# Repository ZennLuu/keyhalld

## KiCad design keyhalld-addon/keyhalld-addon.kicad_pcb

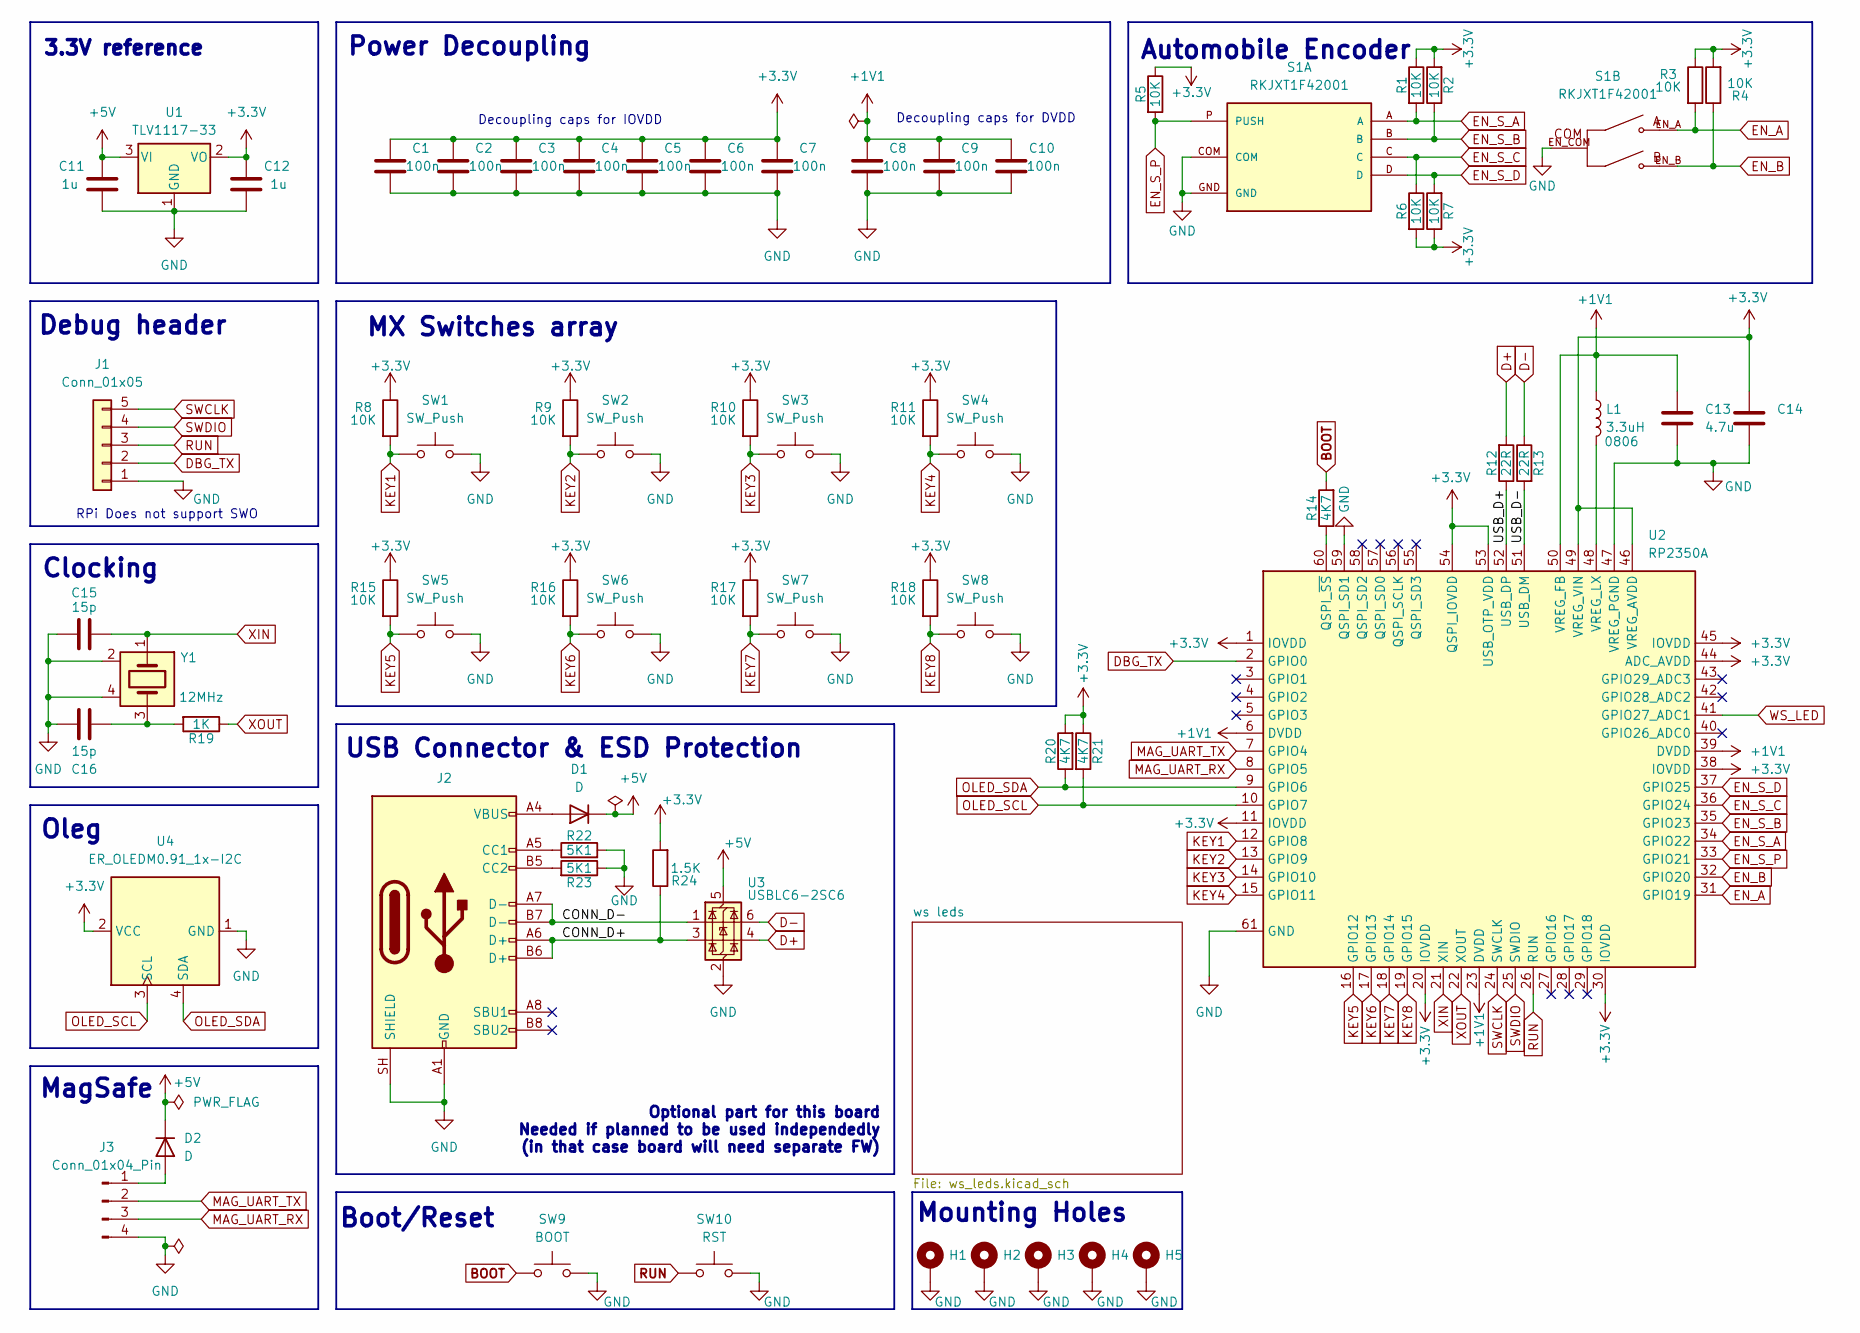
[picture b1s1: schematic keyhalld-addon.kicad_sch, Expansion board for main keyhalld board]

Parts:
C1, C2, C3, C4, C5, C6, C7, C8, C9, C10: 100n; C_0603_1608Metric_Pad1.08x0.95mm_HandSolder
C11, C12: 1u; C_0603_1608Metric_Pad1.08x0.95mm_HandSolder
C13, C14: 4.7u; C_0603_1608Metric
C15, C16: 15p; C_0603_1608Metric_Pad1.08x0.95mm_HandSolder
D1, D2: D; D_SOD-323
H1, H2, H3, H4, H5: MountingHole_Pad; MountingHole_2.2mm_M2_DIN965_Pad
J1: Conn_01x05; PinHeader_1x05_P2.54mm_Horizontal
J2: USB_C_Receptacle_USB2.0_16P; USB_C_Receptacle_GCT_USB4105-xx-A_16P_TopMnt_Horizontal
J3: Conn_01x04_Pin; PinHeader_1x04_P2.54mm_Vertical
L1: 3.3uH; L_Murata_DFE201610P
R1, R2, R3, R4, R5, R6, R7, R8, R9, R10, R11, R15, R16, R17, R18: 10K; R_0603_1608Metric_Pad0.98x0.95mm_HandSolder
R12, R13: 22R; R_0603_1608Metric_Pad0.98x0.95mm_HandSolder
R14, R20, R21: 4K7; R_0603_1608Metric_Pad0.98x0.95mm_HandSolder
R19: 1K; R_0603_1608Metric_Pad0.98x0.95mm_HandSolder
R22, R23: 5K1; R_0603_1608Metric_Pad0.98x0.95mm_HandSolder
R24: 1.5K; R_0603_1608Metric_Pad0.98x0.95mm_HandSolder
S1: RKJXT1F42001; XDCR_RKJXT1F42001
SW1, SW2, SW3, SW4, SW5, SW6, SW7, SW8: SW_Push; SW_Hotswap_Kailh_MX_1.00u
SW9: BOOT; SW_Tactile_SPST_NO_Straight_CK_PTS636Sx25SMTRLFS
SW10: RST; SW_Tactile_SPST_NO_Straight_CK_PTS636Sx25SMTRLFS
U1: TLV1117-33; SOT-223-3_TabPin2
U2: RP2350A; rpi_rp2350a_vias; part_uid RP-01HA9H-9K5E8T
U3: USBLC6-2SC6; SOT-23-6
U4: ER_OLEDM0.91_1x-I2C
Y1: 12MHz; Oscillator_SMD_Abracon_ASE-4Pin_3.2x2.5mm; tolerance 30ppm; part_uid RP-01G8X7-GS352B

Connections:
+1V1: C8.1, C9.1, C10.1, C13.1, L1.1, U2.6 (DVDD), U2.23 (DVDD), U2.39 (DVDD), U2.50 (VREG_FB)
+3.3V: C1.1, C2.1, C3.1, C4.1, C5.1, C6.1, C7.1, C12.1, C14.1, R1.1, R2.2, R3.1, R4.2, R5.1, R6.2, R7.1, R8.1, R9.1, R10.1, R11.1, R15.1, R16.1, R17.1, R18.1, R20.2, R21.1, R24.2, U1.2 (VO), U2.1 (IOVDD), U2.11 (IOVDD), U2.20 (IOVDD), U2.30 (IOVDD), U2.38 (IOVDD), U2.44 (ADC_AVDD), U2.45 (IOVDD), U2.46 (VREG_AVDD), U2.49 (VREG_VIN), U2.53 (USB_OTP_VDD), U2.54 (QSPI_IOVDD), U4.2 (VCC)
+5V: C11.1, D1.1 (K), D2.1 (K), U1.3 (VI), U3.5 (VBUS); also elsewhere on the board
/CONN_D+: J2.A6 (D+), J2.B6 (D+), R24.1, U3.3 (I/O2)
/CONN_D-: J2.A7 (D-), J2.B7 (D-), U3.1 (I/O1)
/USB_D+: R12.1, U2.52 (USB_DP)
/USB_D-: R13.2, U2.51 (USB_DM)
BOOT: R14.2, SW9.1
D+: R12.2, U3.4 (I/O2)
D-: R13.1, U3.6 (I/O1)
DBG_TX: J1.2, U2.2 (GPIO0)
EN_A: R3.2, S1.EN_A, U2.31 (GPIO19)
EN_B: R4.1, S1.EN_B, U2.32 (GPIO20)
EN_S_A: R1.2, S1.A, U2.34 (GPIO22)
EN_S_B: R2.1, S1.B, U2.35 (GPIO23)
EN_S_C: R6.1, S1.C, U2.36 (GPIO24)
EN_S_D: R7.2, S1.D, U2.37 (GPIO25)
EN_S_P: R5.2, S1.P (PUSH), U2.33 (GPIO21)
GND: C1.2, C2.2, C3.2, C4.2, C5.2, C6.2, C7.2, C8.2, C9.2, C10.2, C11.2, C12.2, C13.2, C14.2, C15.1, C16.1, H1.1 (1_1), H2.1 (1_1), H3.1 (1_1), H4.1 (1_1), H5.1 (1_1), J1.1, J2.A1 (GND), J2.A12 (GND), J2.B1 (GND), J2.B12 (GND), J2.SH (SHIELD), J3.4, R22.2, R23.1, S1.COM, S1.EN_COM, S1.GND, SW1.2, SW2.2, SW3.2, SW4.2, SW5.2, SW6.2, SW7.2, SW8.2, SW9.2, SW10.2, U1.1 (GND), U2.47 (VREG_PGND), U2.59 (QSPI_SD1), U2.61 (GND), U3.2 (GND), U4.1 (GND), Y1.2, Y1.4; also elsewhere on the board
KEY1: R8.2, SW1.1, U2.12 (GPIO8)
KEY2: R9.2, SW2.1, U2.13 (GPIO9)
KEY3: R10.2, SW3.1, U2.14 (GPIO10)
KEY4: R11.2, SW4.1, U2.15 (GPIO11)
KEY5: R15.2, SW5.1, U2.16 (GPIO12)
KEY6: R16.2, SW6.1, U2.17 (GPIO13)
KEY7: R17.2, SW7.1, U2.18 (GPIO14)
KEY8: R18.2, SW8.1, U2.19 (GPIO15)
MAG_UART_RX: J3.3, U2.8 (GPIO5)
MAG_UART_TX: J3.2, U2.7 (GPIO4)
unnamed: C16.2, R19.2, Y1.3
unnamed: D1.2 (A), J2.A4 (VBUS), J2.A9 (VBUS), J2.B4 (VBUS), J2.B9 (VBUS)
unnamed: D2.2 (A), J3.1
unnamed: J2.A5 (CC1), R22.1
unnamed: J2.B5 (CC2), R23.2
unnamed: R14.1, U2.60 (QSPI_~SS)
unnamed: L1.2, U2.48 (VREG_LX)
OLED_SCL: R21.2, U2.10 (GPIO7), U4.3 (SCL)
OLED_SDA: R20.1, U2.9 (GPIO6), U4.4 (SDA)
RUN: J1.3, SW10.1, U2.26 (RUN)
SWCLK: J1.5, U2.24 (SWCLK)
SWDIO: J1.4, U2.25 (SWDIO)
WS_LED: U2.41 (GPIO27_ADC1); also elsewhere on the board
XIN: C15.2, U2.21 (XIN), Y1.1
XOUT: R19.1, U2.22 (XOUT)

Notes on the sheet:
Automobile Encoder
Decoupling caps for IOVDD
Boot/Reset
Decoupling caps for DVDD
USB Connector & ESD Protection
Clocking
Oleg
RPi Does not support SWO
MX Switches array
Power Decoupling
Debug header
Mounting Holes
3.3V reference
MagSafe
Optional part for this board Needed if planned to be used independedly (in that case board will need separate FW)

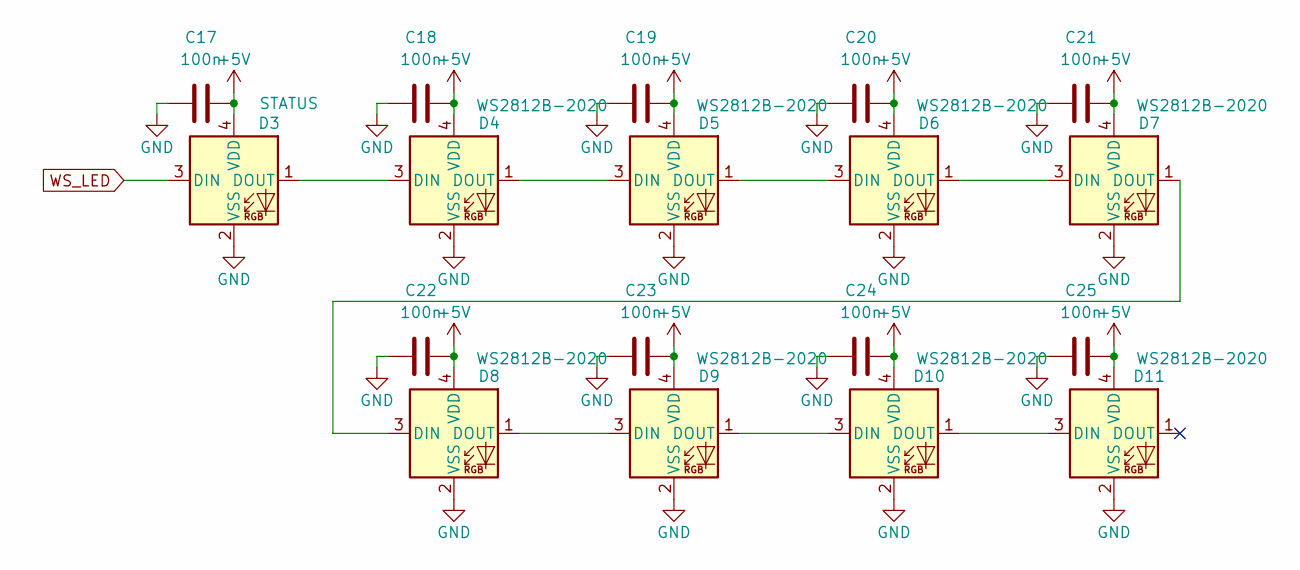
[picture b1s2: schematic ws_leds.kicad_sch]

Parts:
C17, C18, C19, C20, C21, C22, C23, C24, C25: 100n; C_0603_1608Metric
D3: STATUS; LED_WS2812B-2020_PLCC4_2.0x2.0mm
D4, D5, D6, D7, D8, D9, D10, D11: WS2812B-2020; LED_WS2812B-2020_PLCC4_2.0x2.0mm

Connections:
+5V: C17.2, C18.2, C19.2, C20.2, C21.2, C22.2, C23.2, C24.2, C25.2, D3.4 (VDD), D4.4 (VDD), D5.4 (VDD), D6.4 (VDD), D7.4 (VDD), D8.4 (VDD), D9.4 (VDD), D10.4 (VDD), D11.4 (VDD); also elsewhere on the board
GND: C17.1, C18.1, C19.1, C20.1, C21.1, C22.1, C23.1, C24.1, C25.1, D3.2 (VSS), D4.2 (VSS), D5.2 (VSS), D6.2 (VSS), D7.2 (VSS), D8.2 (VSS), D9.2 (VSS), D10.2 (VSS), D11.2 (VSS); also elsewhere on the board
unnamed: D3.1 (DOUT), D4.3 (DIN)
unnamed: D4.1 (DOUT), D5.3 (DIN)
unnamed: D5.1 (DOUT), D6.3 (DIN)
unnamed: D6.1 (DOUT), D7.3 (DIN)
unnamed: D7.1 (DOUT), D8.3 (DIN)
unnamed: D8.1 (DOUT), D9.3 (DIN)
unnamed: D9.1 (DOUT), D10.3 (DIN)
unnamed: D10.1 (DOUT), D11.3 (DIN)
WS_LED: D3.3 (DIN); also elsewhere on the board

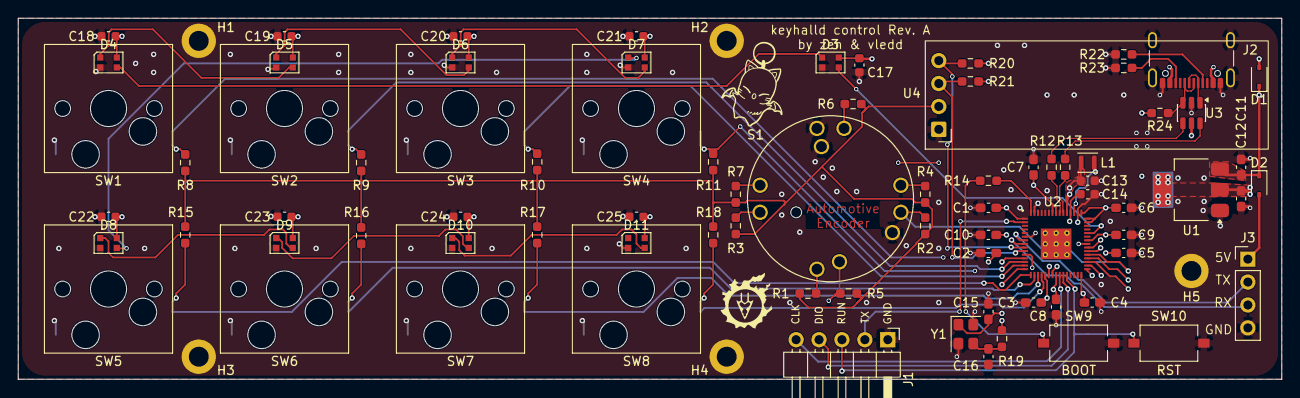
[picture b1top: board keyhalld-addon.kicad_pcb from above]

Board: 4 copper layers, 140.0 x 40.0 mm, 85 parts (0 on the bottom side), 52 nets.

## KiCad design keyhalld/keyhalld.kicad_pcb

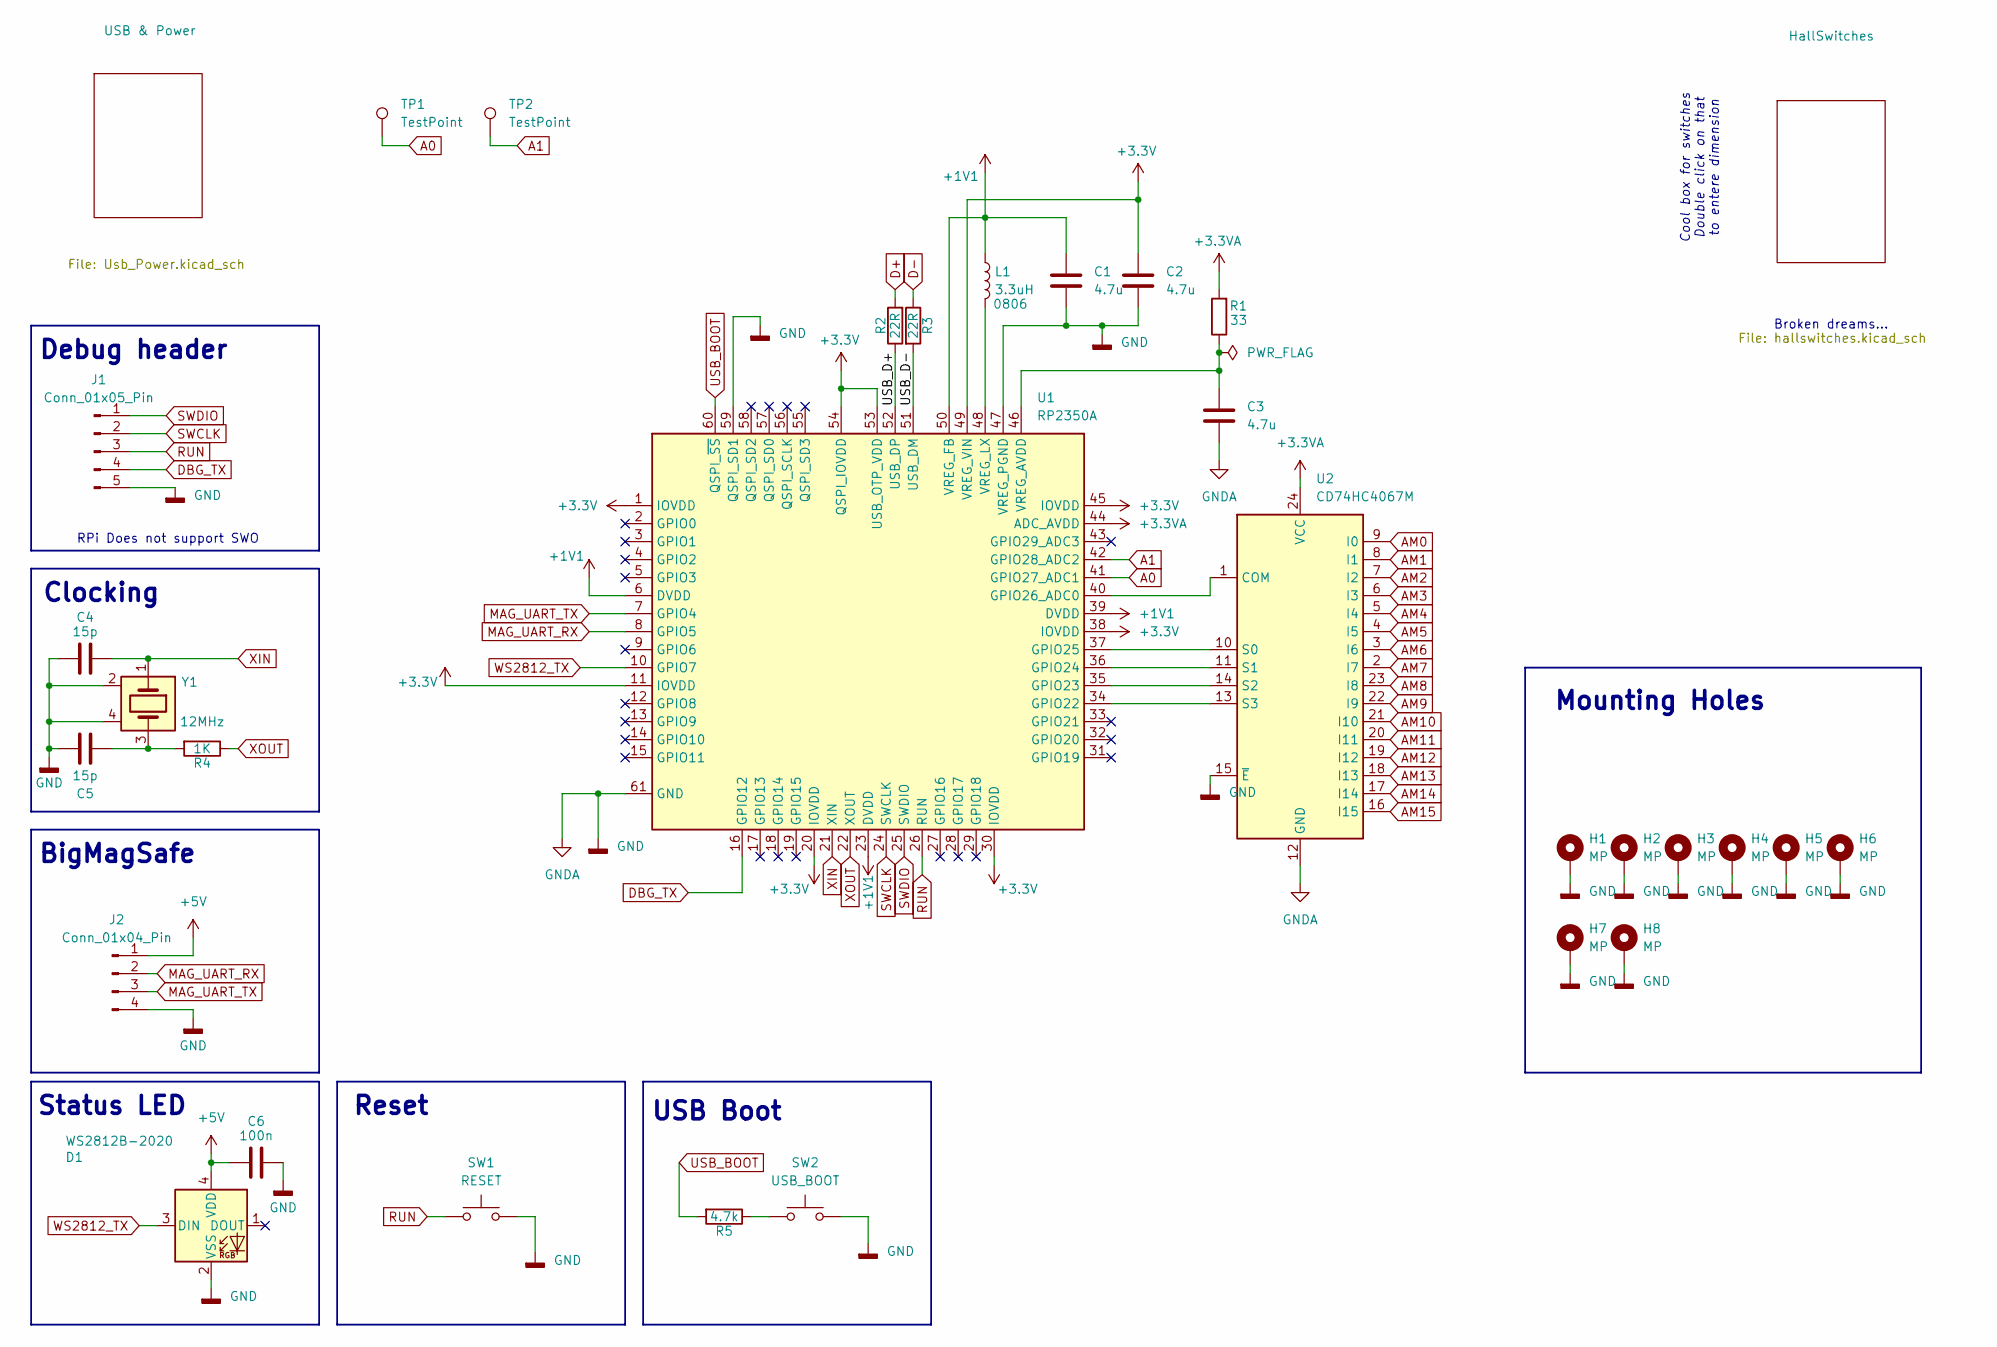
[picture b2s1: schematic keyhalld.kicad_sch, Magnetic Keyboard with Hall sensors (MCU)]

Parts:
C1, C2, C3: 4.7u; C_0603_1608Metric
C4, C5: 15p; C_0603_1608Metric_Pad1.08x0.95mm_HandSolder
C6: 100n; C_0603_1608Metric_Pad1.08x0.95mm_HandSolder
D1: WS2812B-2020; LED_WS2812B-2020_PLCC4_2.0x2.0mm
H1, H2, H3, H4, H5, H6, H7, H8: MP; MountingHole_3.2mm_M3_Pad
J1: Conn_01x05_Pin; PinHeader_1x05_P2.54mm_Horizontal
J2: Conn_01x04_Pin; PinHeader_1x04_P2.54mm_Vertical
L1: 3.3uH; L_Murata_DFE201610P
R1: 33; R_0603_1608Metric_Pad0.98x0.95mm_HandSolder
R2, R3: 22R; R_0603_1608Metric_Pad0.98x0.95mm_HandSolder
R4: 1K; R_0603_1608Metric_Pad0.98x0.95mm_HandSolder
R5: 4.7k; R_0603_1608Metric_Pad0.98x0.95mm_HandSolder
SW1: RESET; SW_Tactile_SPST_NO_Straight_CK_PTS636Sx25SMTRLFS
SW2: USB_BOOT; SW_Tactile_SPST_NO_Straight_CK_PTS636Sx25SMTRLFS
TP1, TP2: TestPoint; TestPoint_Pad_D1.0mm
U1: RP2350A; rpi_rp2350a_vias; part_uid RP-01HA9H-9K5E8T
U2: CD74HC4067M; SOIC-24W_7.5x15.4mm_P1.27mm
Y1: 12MHz; Oscillator_SMD_Abracon_ASE-4Pin_3.2x2.5mm; tolerance 30ppm; part_uid RP-01G8X7-GS352B

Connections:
+1V1: C1.1, L1.1, U1.6 (DVDD), U1.23 (DVDD), U1.39 (DVDD), U1.50 (VREG_FB); also elsewhere on the board
+3.3V: C2.1, U1.1 (IOVDD), U1.11 (IOVDD), U1.20 (IOVDD), U1.30 (IOVDD), U1.38 (IOVDD), U1.45 (IOVDD), U1.49 (VREG_VIN), U1.53 (USB_OTP_VDD), U1.54 (QSPI_IOVDD); also elsewhere on the board
+3.3VA: R1.2, U1.44 (ADC_AVDD), U2.24 (VCC); also elsewhere on the board
+5V: C6.1, D1.4 (VDD), J2.1; also elsewhere on the board
/USB_D+: R2.1, U1.52 (USB_DP)
/USB_D-: R3.2, U1.51 (USB_DM)
A0: TP1.1 (1_1), U1.41 (GPIO27_ADC1); also elsewhere on the board
A1: TP2.1 (1_1), U1.42 (GPIO28_ADC2); also elsewhere on the board
AM0: U2.9 (I0); also elsewhere on the board
AM1: U2.8 (I1); also elsewhere on the board
AM2: U2.7 (I2); also elsewhere on the board
AM3: U2.6 (I3); also elsewhere on the board
AM4: U2.5 (I4); also elsewhere on the board
AM5: U2.4 (I5); also elsewhere on the board
AM6: U2.3 (I6); also elsewhere on the board
AM7: U2.2 (I7); also elsewhere on the board
AM8: U2.23 (I8); also elsewhere on the board
AM9: U2.22 (I9); also elsewhere on the board
AM10: U2.21 (I10); also elsewhere on the board
AM11: U2.20 (I11); also elsewhere on the board
AM12: U2.19 (I12); also elsewhere on the board
AM13: U2.18 (I13); also elsewhere on the board
AM14: U2.17 (I14); also elsewhere on the board
AM15: U2.16 (I15); also elsewhere on the board
D+: R2.2; also elsewhere on the board
D-: R3.1; also elsewhere on the board
DBG_TX: J1.4, U1.16 (GPIO12)
GND: C1.2, C2.2, C3.2, C4.1, C5.1, C6.2, D1.2 (VSS), H1.1 (1_1), H2.1 (1_1), H3.1 (1_1), H4.1 (1_1), H5.1 (1_1), H6.1 (1_1), H7.1 (1_1), H8.1 (1_1), J1.5, J2.4, SW1.2, SW2.2, U1.47 (VREG_PGND), U1.59 (QSPI_SD1), U1.61 (GND), U2.12 (GND), U2.15 (~E), Y1.2, Y1.4; also elsewhere on the board
MAG_UART_RX: J2.2, U1.8 (GPIO5)
MAG_UART_TX: J2.3, U1.7 (GPIO4)
unnamed: C5.2, R4.2, Y1.3
unnamed: R5.1, SW2.1
unnamed: U1.34 (GPIO22), U2.13 (S3)
unnamed: U1.35 (GPIO23), U2.14 (S2)
unnamed: U1.36 (GPIO24), U2.11 (S1)
unnamed: U1.37 (GPIO25), U2.10 (S0)
unnamed: U1.40 (GPIO26_ADC0), U2.1 (COM)
unnamed: C3.1, R1.1, U1.46 (VREG_AVDD)
unnamed: L1.2, U1.48 (VREG_LX)
RUN: J1.3, SW1.1, U1.26 (RUN)
SWCLK: J1.2, U1.24 (SWCLK)
SWDIO: J1.1, U1.25 (SWDIO)
USB_BOOT: R5.2, U1.60 (QSPI_~SS)
WS2812_TX: D1.3 (DIN), U1.10 (GPIO7)
XIN: C4.2, U1.21 (XIN), Y1.1
XOUT: R4.1, U1.22 (XOUT)

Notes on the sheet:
RPi Does not support SWO
BigMagSafe
Clocking
Cool box for switches Double click on that to entere dimension
Reset
Status LED
Debug header
Mounting Holes
USB Boot
Broken dreams...

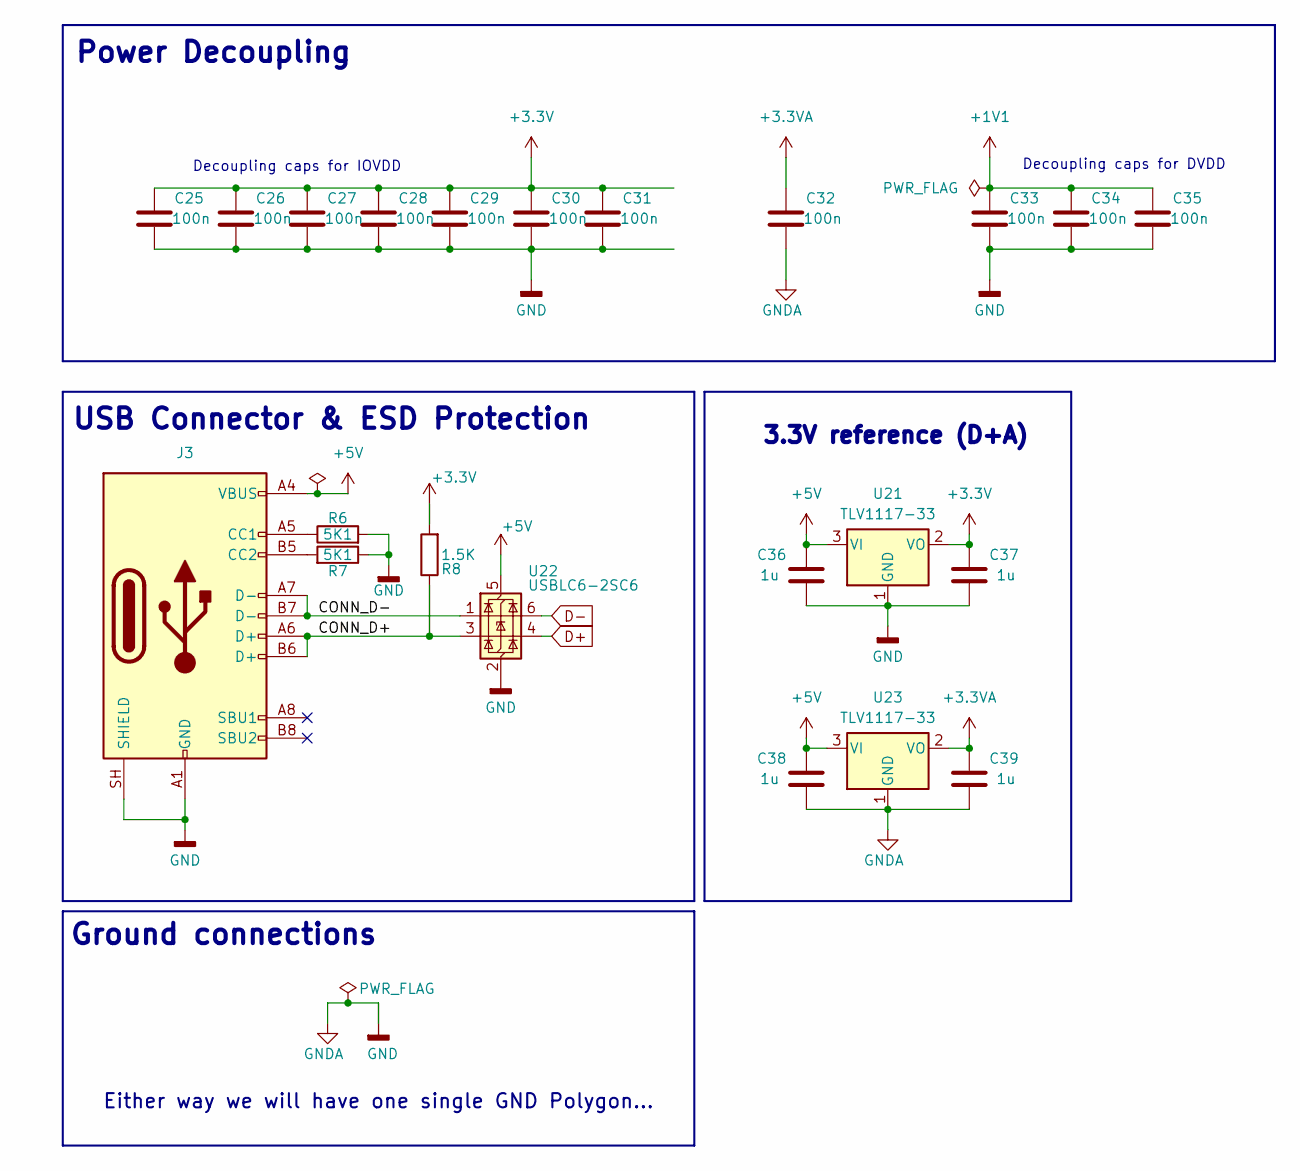
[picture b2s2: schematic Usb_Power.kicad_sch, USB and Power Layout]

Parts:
C25, C26, C27, C28, C29, C30, C31, C32, C33, C34, C35: 100n; C_0603_1608Metric_Pad1.08x0.95mm_HandSolder
C36, C37, C38, C39: 1u; C_0603_1608Metric_Pad1.08x0.95mm_HandSolder
J3: USB_C_Receptacle_USB2.0_16P; USB_C_Receptacle_GCT_USB4105-xx-A_16P_TopMnt_Horizontal
R6, R7: 5K1; R_0603_1608Metric_Pad0.98x0.95mm_HandSolder
R8: 1.5K; R_0603_1608Metric_Pad0.98x0.95mm_HandSolder
U21, U23: TLV1117-33; SOT-223
U22: USBLC6-2SC6; SOT-23-6

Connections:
+1V1: C33.1, C34.1, C35.1; also elsewhere on the board
+3.3V: C25.1, C26.1, C27.1, C28.1, C29.1, C30.1, C31.1, C37.1, R8.2, U21.2 (VO); also elsewhere on the board
+3.3VA: C32.1, C39.1, U23.2 (VO); also elsewhere on the board
+5V: C36.1, C38.1, J3.A4 (VBUS), J3.A9 (VBUS), J3.B4 (VBUS), J3.B9 (VBUS), U21.3 (VI), U22.5 (VBUS), U23.3 (VI); also elsewhere on the board
/USB & Power/CONN_D+: J3.A6 (D+), J3.B6 (D+), R8.1, U22.3 (I/O2)
/USB & Power/CONN_D-: J3.A7 (D-), J3.B7 (D-), U22.1 (I/O1)
D+: U22.4 (I/O2); also elsewhere on the board
D-: U22.6 (I/O1); also elsewhere on the board
GND: C25.2, C26.2, C27.2, C28.2, C29.2, C30.2, C31.2, C32.2, C33.2, C34.2, C35.2, C36.2, C37.2, C38.2, C39.2, J3.A1 (GND), J3.A12 (GND), J3.B1 (GND), J3.B12 (GND), J3.SH (SHIELD), R6.2, R7.1, U21.1 (GND), U22.2 (GND), U23.1 (GND); also elsewhere on the board
unnamed: J3.A5 (CC1), R6.1
unnamed: J3.B5 (CC2), R7.2

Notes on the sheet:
Power Decoupling
Decoupling caps for IOVDD
3.3V reference (D+A)
Ground connections
Decoupling caps for DVDD
USB Connector & ESD Protection
Either way we will have one single GND Polygon...

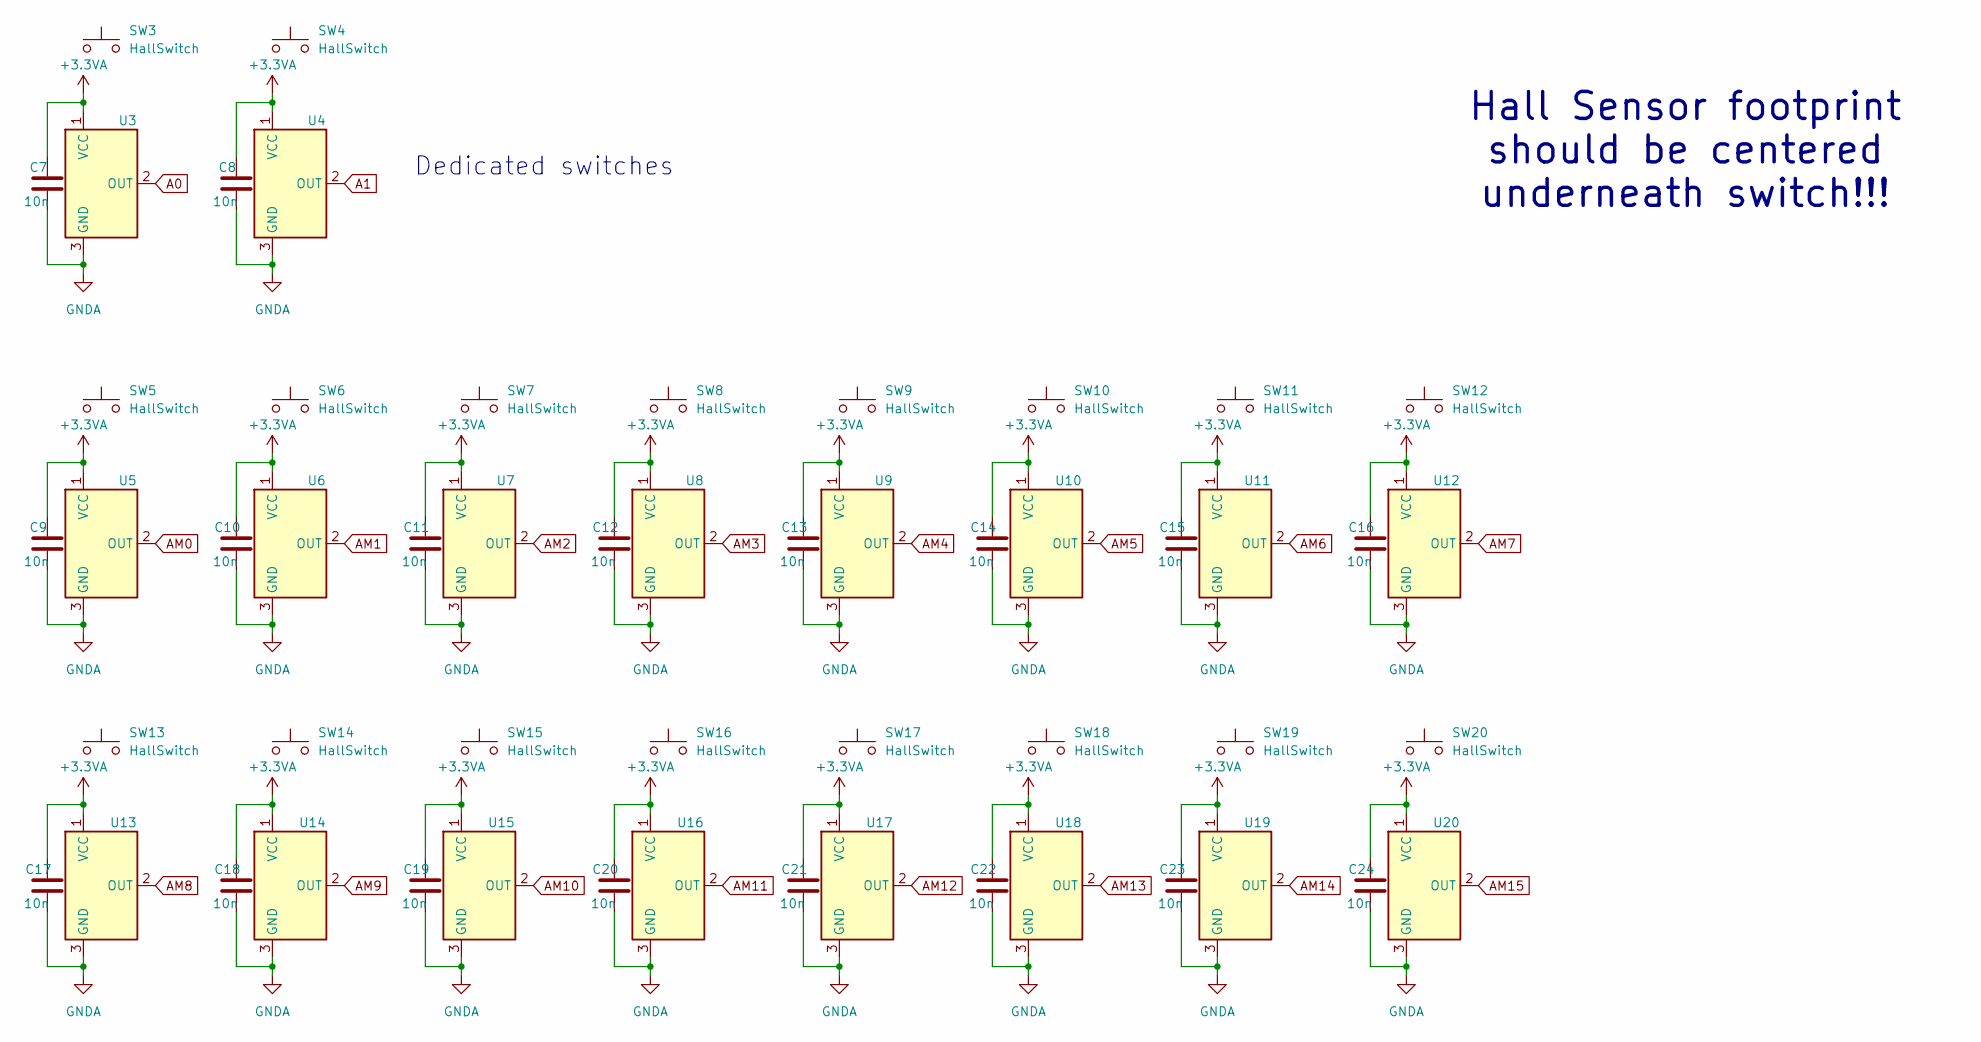
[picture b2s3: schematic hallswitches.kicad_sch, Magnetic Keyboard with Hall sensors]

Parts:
C7, C8, C9, C10, C11, C12, C13, C14, C15, C16, C17, C18, C19, C20, C21, C22, C23, C24: 10n; C_0603_1608Metric_Pad1.08x0.95mm_HandSolder
SW3, SW4, SW5, SW6, SW7, SW8, SW9, SW10, SW11, SW12, SW13, SW14, SW15, SW16, SW17, SW18, SW19, SW20: HallSwitch; Custom_MX_PCB_1.00u
U3, U4, U5, U6, U7, U8, U9, U10, U11, U12, U13, U14, U15, U16, U17, U18, U19, U20: DRV5055A4xDBZxQ1; SOT-23

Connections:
+3.3VA: C7.2, C8.2, C9.2, C10.2, C11.2, C12.2, C13.2, C14.2, C15.2, C16.2, C17.2, C18.2, C19.2, C20.2, C21.2, C22.2, C23.2, C24.2, U3.1 (VCC), U4.1 (VCC), U5.1 (VCC), U6.1 (VCC), U7.1 (VCC), U8.1 (VCC), U9.1 (VCC), U10.1 (VCC), U11.1 (VCC), U12.1 (VCC), U13.1 (VCC), U14.1 (VCC), U15.1 (VCC), U16.1 (VCC), U17.1 (VCC), U18.1 (VCC), U19.1 (VCC), U20.1 (VCC); also elsewhere on the board
A0: U3.2 (OUT); also elsewhere on the board
A1: U4.2 (OUT); also elsewhere on the board
AM0: U5.2 (OUT); also elsewhere on the board
AM1: U6.2 (OUT); also elsewhere on the board
AM2: U7.2 (OUT); also elsewhere on the board
AM3: U8.2 (OUT); also elsewhere on the board
AM4: U9.2 (OUT); also elsewhere on the board
AM5: U10.2 (OUT); also elsewhere on the board
AM6: U11.2 (OUT); also elsewhere on the board
AM7: U12.2 (OUT); also elsewhere on the board
AM8: U13.2 (OUT); also elsewhere on the board
AM9: U14.2 (OUT); also elsewhere on the board
AM10: U15.2 (OUT); also elsewhere on the board
AM11: U16.2 (OUT); also elsewhere on the board
AM12: U17.2 (OUT); also elsewhere on the board
AM13: U18.2 (OUT); also elsewhere on the board
AM14: U19.2 (OUT); also elsewhere on the board
AM15: U20.2 (OUT); also elsewhere on the board
GND: C7.1, C8.1, C9.1, C10.1, C11.1, C12.1, C13.1, C14.1, C15.1, C16.1, C17.1, C18.1, C19.1, C20.1, C21.1, C22.1, C23.1, C24.1, U3.3 (GND), U4.3 (GND), U5.3 (GND), U6.3 (GND), U7.3 (GND), U8.3 (GND), U9.3 (GND), U10.3 (GND), U11.3 (GND), U12.3 (GND), U13.3 (GND), U14.3 (GND), U15.3 (GND), U16.3 (GND), U17.3 (GND), U18.3 (GND), U19.3 (GND), U20.3 (GND); also elsewhere on the board

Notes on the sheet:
Hall Sensor footprint should be centered underneath switch!!!
Dedicated switches

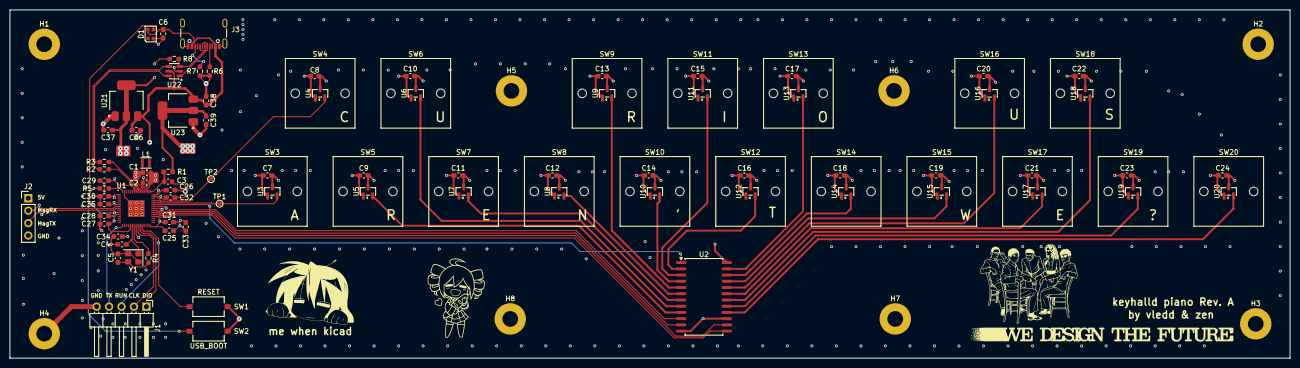
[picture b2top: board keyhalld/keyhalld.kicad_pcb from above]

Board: 4 copper layers, 261.0 x 71.0 mm, 107 parts (0 on the bottom side), 50 nets.

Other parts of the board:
G1: me when kicad; LOGO
